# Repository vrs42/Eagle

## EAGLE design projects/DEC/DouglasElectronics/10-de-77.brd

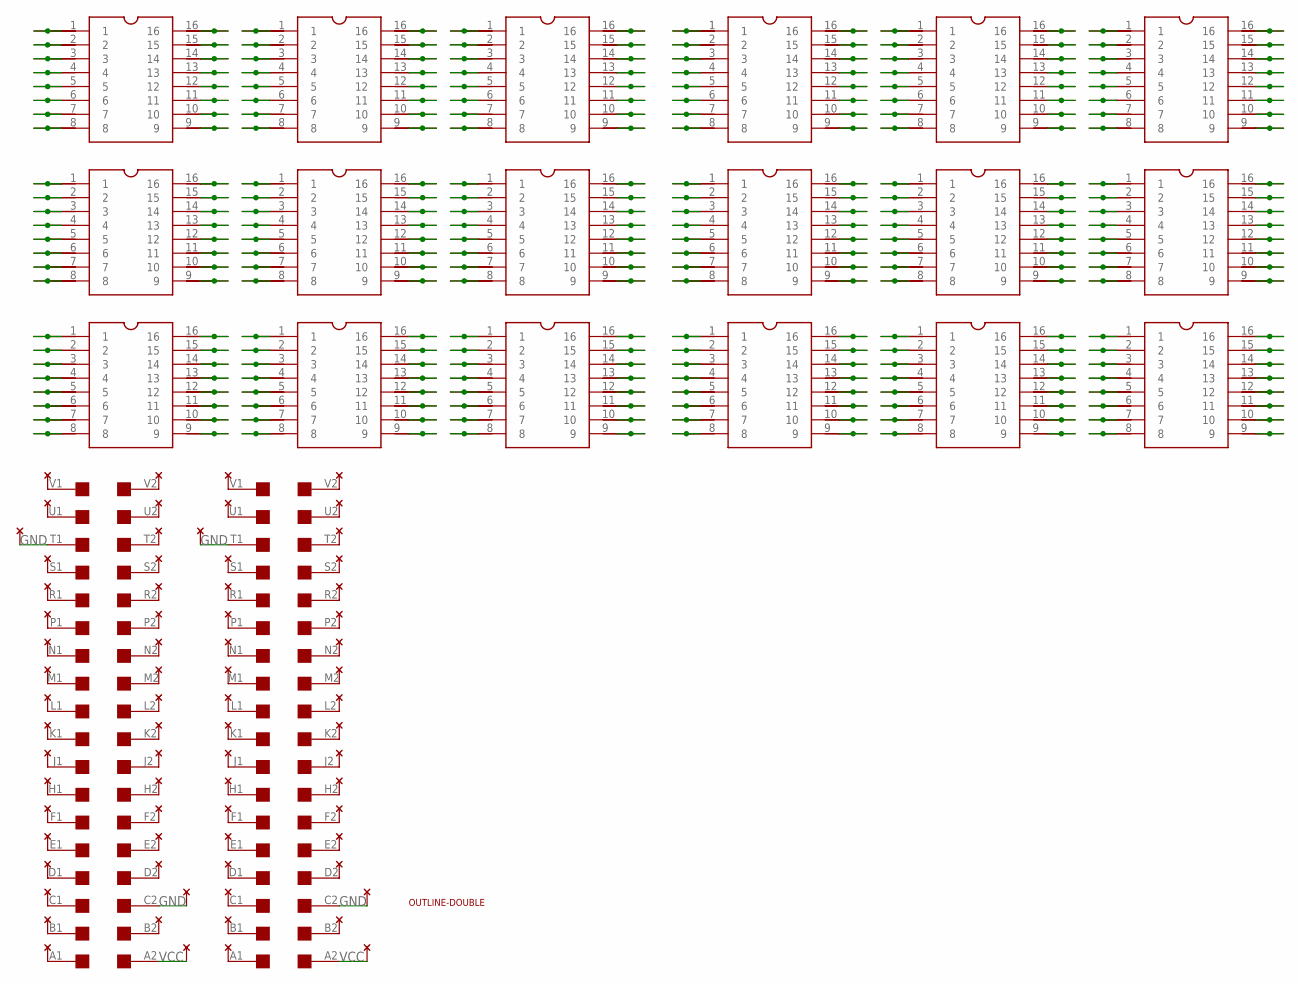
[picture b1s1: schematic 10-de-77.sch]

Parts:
U$1, U$6: SINGLE; EDGE-CON2
U$4: OUTLINE-DOUBLE; DOUBLE
U$5, U$7, U$8, U$9, U$10, U$11, U$12, U$13, U$14, U$15, U$16, U$17, U$18, U$19, U$20, U$21, U$22, U$23: DIL16PROTO
U$24, U$25, U$26, U$27: THRU-HOLE1A

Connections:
GND: U$1.C2, U$1.T1, U$6.C2, U$6.T1, U$24.T1, U$25.C1, U$26.T1, U$27.C1
unnamed: U$1.K2, U$25.K1
unnamed: U$1.J2, U$25.J1
unnamed: U$1.H2, U$25.H1
unnamed: U$1.L2, U$25.L1
unnamed: U$1.M2, U$25.M1
unnamed: U$1.N2, U$25.N1
unnamed: U$1.P2, U$25.P1
unnamed: U$1.F2, U$25.F1
unnamed: U$1.E2, U$25.E1
unnamed: U$1.D2, U$25.D1
unnamed: U$1.R2, U$25.R1
unnamed: U$1.S2, U$25.S1
unnamed: U$1.B2, U$25.B1
unnamed: U$1.T2, U$25.T1
unnamed: U$1.U2, U$25.U1
unnamed: U$1.V2, U$25.V1
unnamed: U$1.A1, U$24.A1
unnamed: U$1.V1, U$24.V1
unnamed: U$1.U1, U$24.U1
unnamed: U$1.S1, U$24.S1
unnamed: U$1.R1, U$24.R1
unnamed: U$1.P1, U$24.P1
unnamed: U$1.N1, U$24.N1
unnamed: U$1.M1, U$24.M1
unnamed: U$1.L1, U$24.L1
unnamed: U$1.K1, U$24.K1
unnamed: U$1.J1, U$24.J1
unnamed: U$1.H1, U$24.H1
unnamed: U$1.F1, U$24.F1
unnamed: U$1.E1, U$24.E1
unnamed: U$1.D1, U$24.D1
unnamed: U$1.C1, U$24.C1
unnamed: U$1.B1, U$24.B1
unnamed: U$6.K2, U$27.K1
unnamed: U$6.J2, U$27.J1
unnamed: U$6.H2, U$27.H1
unnamed: U$6.L2, U$27.L1
unnamed: U$6.M2, U$27.M1
unnamed: U$6.N2, U$27.N1
unnamed: U$6.P2, U$27.P1
unnamed: U$6.F2, U$27.F1
unnamed: U$6.E2, U$27.E1
unnamed: U$6.D2, U$27.D1
unnamed: U$6.R2, U$27.R1
unnamed: U$6.S2, U$27.S1
unnamed: U$6.B2, U$27.B1
unnamed: U$6.T2, U$27.T1
unnamed: U$6.U2, U$27.U1
unnamed: U$6.V2, U$27.V1
unnamed: U$6.A1, U$26.A1
unnamed: U$6.V1, U$26.V1
unnamed: U$6.U1, U$26.U1
unnamed: U$6.S1, U$26.S1
unnamed: U$6.R1, U$26.R1
unnamed: U$6.P1, U$26.P1
unnamed: U$6.N1, U$26.N1
unnamed: U$6.M1, U$26.M1
unnamed: U$6.L1, U$26.L1
unnamed: U$6.K1, U$26.K1
unnamed: U$6.J1, U$26.J1
unnamed: U$6.H1, U$26.H1
unnamed: U$6.F1, U$26.F1
unnamed: U$6.E1, U$26.E1
unnamed: U$6.D1, U$26.D1
unnamed: U$6.C1, U$26.C1
unnamed: U$6.B1, U$26.B1
unnamed: U$5.1, U$5.1@2 (1), U$5.1@3 (1)
unnamed: U$5.4, U$5.4@2 (4), U$5.4@3 (4)
unnamed: U$5.2, U$5.2@2 (2), U$5.2@3 (2)
unnamed: U$5.3, U$5.3@2 (3), U$5.3@3 (3)
unnamed: U$5.5, U$5.5@2 (5), U$5.5@3 (5)
unnamed: U$5.6, U$5.6@2 (6), U$5.6@3 (6)
unnamed: U$5.7, U$5.7@2 (7), U$5.7@3 (7)
unnamed: U$5.8, U$5.8@2 (8), U$5.8@3 (8)
unnamed: U$5.16, U$5.16@2 (16), U$5.16@3 (16)
unnamed: U$5.15, U$5.15@2 (15), U$5.15@3 (15)
unnamed: U$5.14, U$5.14@2 (14), U$5.14@3 (14)
unnamed: U$5.13, U$5.13@2 (13), U$5.13@3 (13)
unnamed: U$5.12, U$5.12@2 (12), U$5.12@3 (12)
unnamed: U$5.11, U$5.11@2 (11), U$5.11@3 (11)
unnamed: U$5.10, U$5.10@2 (10), U$5.10@3 (10)
unnamed: U$5.9, U$5.9@2 (9), U$5.9@3 (9)
unnamed: U$7.1, U$7.1@2 (1), U$7.1@3 (1)
unnamed: U$7.2, U$7.2@2 (2), U$7.2@3 (2)
unnamed: U$7.3, U$7.3@2 (3), U$7.3@3 (3)
unnamed: U$7.4, U$7.4@2 (4), U$7.4@3 (4)
unnamed: U$7.5, U$7.5@2 (5), U$7.5@3 (5)
unnamed: U$7.6, U$7.6@2 (6), U$7.6@3 (6)
unnamed: U$7.7, U$7.7@2 (7), U$7.7@3 (7)
unnamed: U$7.8, U$7.8@2 (8), U$7.8@3 (8)
unnamed: U$7.16, U$7.16@2 (16), U$7.16@3 (16)
unnamed: U$7.15, U$7.15@2 (15), U$7.15@3 (15)
unnamed: U$7.14, U$7.14@2 (14), U$7.14@3 (14)
unnamed: U$7.13, U$7.13@2 (13), U$7.13@3 (13)
unnamed: U$7.12, U$7.12@2 (12), U$7.12@3 (12)
unnamed: U$7.11, U$7.11@2 (11), U$7.11@3 (11)
unnamed: U$7.10, U$7.10@2 (10), U$7.10@3 (10)
unnamed: U$7.9, U$7.9@2 (9), U$7.9@3 (9)
unnamed: U$8.1, U$8.1@2 (1), U$8.1@3 (1)
unnamed: U$8.2, U$8.2@2 (2), U$8.2@3 (2)
unnamed: U$8.3, U$8.3@2 (3), U$8.3@3 (3)
unnamed: U$8.4, U$8.4@2 (4), U$8.4@3 (4)
unnamed: U$8.5, U$8.5@2 (5), U$8.5@3 (5)
unnamed: U$8.6, U$8.6@2 (6), U$8.6@3 (6)
unnamed: U$8.7, U$8.7@2 (7), U$8.7@3 (7)
unnamed: U$8.8, U$8.8@2 (8), U$8.8@3 (8)
unnamed: U$8.16, U$8.16@2 (16), U$8.16@3 (16)
unnamed: U$8.15, U$8.15@2 (15), U$8.15@3 (15)
unnamed: U$8.14, U$8.14@2 (14), U$8.14@3 (14)
unnamed: U$8.13, U$8.13@2 (13), U$8.13@3 (13)
unnamed: U$8.12, U$8.12@2 (12), U$8.12@3 (12)
unnamed: U$8.11, U$8.11@2 (11), U$8.11@3 (11)
unnamed: U$8.10, U$8.10@2 (10), U$8.10@3 (10)
unnamed: U$8.9, U$8.9@2 (9), U$8.9@3 (9)
unnamed: U$9.1, U$9.1@2 (1), U$9.1@3 (1)
unnamed: U$9.2, U$9.2@2 (2), U$9.2@3 (2)
unnamed: U$9.3, U$9.3@2 (3), U$9.3@3 (3)
unnamed: U$9.4, U$9.4@2 (4), U$9.4@3 (4)
unnamed: U$9.5, U$9.5@2 (5), U$9.5@3 (5)
unnamed: U$9.6, U$9.6@2 (6), U$9.6@3 (6)
unnamed: U$9.7, U$9.7@2 (7), U$9.7@3 (7)
unnamed: U$9.8, U$9.8@2 (8), U$9.8@3 (8)
unnamed: U$9.16, U$9.16@2 (16), U$9.16@3 (16)
unnamed: U$9.15, U$9.15@2 (15), U$9.15@3 (15)
unnamed: U$9.14, U$9.14@2 (14), U$9.14@3 (14)
unnamed: U$9.13, U$9.13@2 (13), U$9.13@3 (13)
unnamed: U$9.12, U$9.12@2 (12), U$9.12@3 (12)
unnamed: U$9.11, U$9.11@2 (11), U$9.11@3 (11)
unnamed: U$9.10, U$9.10@2 (10), U$9.10@3 (10)
unnamed: U$9.9, U$9.9@2 (9), U$9.9@3 (9)
unnamed: U$10.1, U$10.1@2 (1), U$10.1@3 (1)
unnamed: U$10.2, U$10.2@2 (2), U$10.2@3 (2)
unnamed: U$10.3, U$10.3@2 (3), U$10.3@3 (3)
unnamed: U$10.4, U$10.4@2 (4), U$10.4@3 (4)
unnamed: U$10.5, U$10.5@2 (5), U$10.5@3 (5)
unnamed: U$10.6, U$10.6@2 (6), U$10.6@3 (6)
unnamed: U$10.7, U$10.7@2 (7), U$10.7@3 (7)
unnamed: U$10.8, U$10.8@2 (8), U$10.8@3 (8)
unnamed: U$10.16, U$10.16@2 (16), U$10.16@3 (16)
unnamed: U$10.15, U$10.15@2 (15), U$10.15@3 (15)
unnamed: U$10.14, U$10.14@2 (14), U$10.14@3 (14)
unnamed: U$10.13, U$10.13@2 (13), U$10.13@3 (13)
unnamed: U$10.12, U$10.12@2 (12), U$10.12@3 (12)
unnamed: U$10.11, U$10.11@2 (11), U$10.11@3 (11)
unnamed: U$10.10, U$10.10@2 (10), U$10.10@3 (10)
unnamed: U$10.9, U$10.9@2 (9), U$10.9@3 (9)
unnamed: U$11.1, U$11.1@2 (1), U$11.1@3 (1)
unnamed: U$11.2, U$11.2@2 (2), U$11.2@3 (2)
unnamed: U$11.3, U$11.3@2 (3), U$11.3@3 (3)
unnamed: U$11.4, U$11.4@2 (4), U$11.4@3 (4)
unnamed: U$11.5, U$11.5@2 (5), U$11.5@3 (5)
unnamed: U$11.6, U$11.6@2 (6), U$11.6@3 (6)
unnamed: U$11.7, U$11.7@2 (7), U$11.7@3 (7)
unnamed: U$11.8, U$11.8@2 (8), U$11.8@3 (8)
unnamed: U$11.16, U$11.16@2 (16), U$11.16@3 (16)
unnamed: U$11.15, U$11.15@2 (15), U$11.15@3 (15)
unnamed: U$11.14, U$11.14@2 (14), U$11.14@3 (14)
unnamed: U$11.13, U$11.13@2 (13), U$11.13@3 (13)
unnamed: U$11.12, U$11.12@2 (12), U$11.12@3 (12)
unnamed: U$11.11, U$11.11@2 (11), U$11.11@3 (11)
unnamed: U$11.10, U$11.10@2 (10), U$11.10@3 (10)
unnamed: U$11.9, U$11.9@2 (9), U$11.9@3 (9)
unnamed: U$12.1, U$12.1@2 (1), U$12.1@3 (1)
unnamed: U$12.2, U$12.2@2 (2), U$12.2@3 (2)
unnamed: U$12.3, U$12.3@2 (3), U$12.3@3 (3)
unnamed: U$12.4, U$12.4@2 (4), U$12.4@3 (4)
unnamed: U$12.5, U$12.5@2 (5), U$12.5@3 (5)
unnamed: U$12.6, U$12.6@2 (6), U$12.6@3 (6)
unnamed: U$12.7, U$12.7@2 (7), U$12.7@3 (7)
unnamed: U$12.8, U$12.8@2 (8), U$12.8@3 (8)
unnamed: U$12.16, U$12.16@2 (16), U$12.16@3 (16)
unnamed: U$12.15, U$12.15@2 (15), U$12.15@3 (15)
unnamed: U$12.14, U$12.14@2 (14), U$12.14@3 (14)
unnamed: U$12.13, U$12.13@2 (13), U$12.13@3 (13)
unnamed: U$12.12, U$12.12@2 (12), U$12.12@3 (12)
unnamed: U$12.11, U$12.11@2 (11), U$12.11@3 (11)
unnamed: U$12.10, U$12.10@2 (10), U$12.10@3 (10)
unnamed: U$12.9, U$12.9@2 (9), U$12.9@3 (9)
unnamed: U$13.1, U$13.1@2 (1), U$13.1@3 (1)
unnamed: U$13.2, U$13.2@2 (2), U$13.2@3 (2)
unnamed: U$13.3, U$13.3@2 (3), U$13.3@3 (3)
unnamed: U$13.4, U$13.4@2 (4), U$13.4@3 (4)
unnamed: U$13.5, U$13.5@2 (5), U$13.5@3 (5)
unnamed: U$13.6, U$13.6@2 (6), U$13.6@3 (6)
unnamed: U$13.7, U$13.7@2 (7), U$13.7@3 (7)
unnamed: U$13.8, U$13.8@2 (8), U$13.8@3 (8)
unnamed: U$13.16, U$13.16@2 (16), U$13.16@3 (16)
unnamed: U$13.15, U$13.15@2 (15), U$13.15@3 (15)
unnamed: U$13.14, U$13.14@2 (14), U$13.14@3 (14)
unnamed: U$13.13, U$13.13@2 (13), U$13.13@3 (13)
unnamed: U$13.12, U$13.12@2 (12), U$13.12@3 (12)
unnamed: U$13.11, U$13.11@2 (11), U$13.11@3 (11)
unnamed: U$13.10, U$13.10@2 (10), U$13.10@3 (10)
unnamed: U$13.9, U$13.9@2 (9), U$13.9@3 (9)
unnamed: U$14.1, U$14.1@2 (1), U$14.1@3 (1)
unnamed: U$14.2, U$14.2@2 (2), U$14.2@3 (2)
unnamed: U$14.3, U$14.3@2 (3), U$14.3@3 (3)
unnamed: U$14.4, U$14.4@2 (4), U$14.4@3 (4)
unnamed: U$14.5, U$14.5@2 (5), U$14.5@3 (5)
unnamed: U$14.6, U$14.6@2 (6), U$14.6@3 (6)
unnamed: U$14.7, U$14.7@2 (7), U$14.7@3 (7)
unnamed: U$14.8, U$14.8@2 (8), U$14.8@3 (8)
unnamed: U$14.16, U$14.16@2 (16), U$14.16@3 (16)
unnamed: U$14.15, U$14.15@2 (15), U$14.15@3 (15)
unnamed: U$14.14, U$14.14@2 (14), U$14.14@3 (14)
unnamed: U$14.13, U$14.13@2 (13), U$14.13@3 (13)
unnamed: U$14.12, U$14.12@2 (12), U$14.12@3 (12)
unnamed: U$14.11, U$14.11@2 (11), U$14.11@3 (11)
unnamed: U$14.10, U$14.10@2 (10), U$14.10@3 (10)
unnamed: U$14.9, U$14.9@2 (9), U$14.9@3 (9)
unnamed: U$15.1, U$15.1@2 (1), U$15.1@3 (1)
unnamed: U$15.2, U$15.2@2 (2), U$15.2@3 (2)
unnamed: U$15.3, U$15.3@2 (3), U$15.3@3 (3)
unnamed: U$15.4, U$15.4@2 (4), U$15.4@3 (4)
unnamed: U$15.5, U$15.5@2 (5), U$15.5@3 (5)
unnamed: U$15.6, U$15.6@2 (6), U$15.6@3 (6)
unnamed: U$15.7, U$15.7@2 (7), U$15.7@3 (7)
unnamed: U$15.8, U$15.8@2 (8), U$15.8@3 (8)
unnamed: U$15.16, U$15.16@2 (16), U$15.16@3 (16)
unnamed: U$15.15, U$15.15@2 (15), U$15.15@3 (15)
unnamed: U$15.14, U$15.14@2 (14), U$15.14@3 (14)
unnamed: U$15.13, U$15.13@2 (13), U$15.13@3 (13)
unnamed: U$15.12, U$15.12@2 (12), U$15.12@3 (12)
unnamed: U$15.11, U$15.11@2 (11), U$15.11@3 (11)
unnamed: U$15.10, U$15.10@2 (10), U$15.10@3 (10)
unnamed: U$15.9, U$15.9@2 (9), U$15.9@3 (9)
unnamed: U$16.1, U$16.1@2 (1), U$16.1@3 (1)
unnamed: U$16.2, U$16.2@2 (2), U$16.2@3 (2)
unnamed: U$16.3, U$16.3@2 (3), U$16.3@3 (3)
unnamed: U$16.4, U$16.4@2 (4), U$16.4@3 (4)
unnamed: U$16.5, U$16.5@2 (5), U$16.5@3 (5)
unnamed: U$16.6, U$16.6@2 (6), U$16.6@3 (6)
unnamed: U$16.7, U$16.7@2 (7), U$16.7@3 (7)
unnamed: U$16.8, U$16.8@2 (8), U$16.8@3 (8)
unnamed: U$16.16, U$16.16@2 (16), U$16.16@3 (16)
unnamed: U$16.15, U$16.15@2 (15), U$16.15@3 (15)
unnamed: U$16.14, U$16.14@2 (14), U$16.14@3 (14)
unnamed: U$16.13, U$16.13@2 (13), U$16.13@3 (13)
unnamed: U$16.12, U$16.12@2 (12), U$16.12@3 (12)
unnamed: U$16.11, U$16.11@2 (11), U$16.11@3 (11)
unnamed: U$16.10, U$16.10@2 (10), U$16.10@3 (10)
unnamed: U$16.9, U$16.9@2 (9), U$16.9@3 (9)
unnamed: U$17.1, U$17.1@2 (1), U$17.1@3 (1)
unnamed: U$17.2, U$17.2@2 (2), U$17.2@3 (2)
unnamed: U$17.3, U$17.3@2 (3), U$17.3@3 (3)
unnamed: U$17.4, U$17.4@2 (4), U$17.4@3 (4)
unnamed: U$17.5, U$17.5@2 (5), U$17.5@3 (5)
unnamed: U$17.6, U$17.6@2 (6), U$17.6@3 (6)
unnamed: U$17.7, U$17.7@2 (7), U$17.7@3 (7)
unnamed: U$17.8, U$17.8@2 (8), U$17.8@3 (8)
unnamed: U$17.16, U$17.16@2 (16), U$17.16@3 (16)
unnamed: U$17.15, U$17.15@2 (15), U$17.15@3 (15)
unnamed: U$17.14, U$17.14@2 (14), U$17.14@3 (14)
unnamed: U$17.13, U$17.13@2 (13), U$17.13@3 (13)
unnamed: U$17.12, U$17.12@2 (12), U$17.12@3 (12)
unnamed: U$17.11, U$17.11@2 (11), U$17.11@3 (11)
unnamed: U$17.10, U$17.10@2 (10), U$17.10@3 (10)
unnamed: U$17.9, U$17.9@2 (9), U$17.9@3 (9)
unnamed: U$18.1, U$18.1@2 (1), U$18.1@3 (1)
unnamed: U$18.2, U$18.2@2 (2), U$18.2@3 (2)
unnamed: U$18.3, U$18.3@2 (3), U$18.3@3 (3)
unnamed: U$18.4, U$18.4@2 (4), U$18.4@3 (4)
unnamed: U$18.5, U$18.5@2 (5), U$18.5@3 (5)
unnamed: U$18.6, U$18.6@2 (6), U$18.6@3 (6)
unnamed: U$18.7, U$18.7@2 (7), U$18.7@3 (7)
unnamed: U$18.8, U$18.8@2 (8), U$18.8@3 (8)
unnamed: U$18.16, U$18.16@2 (16), U$18.16@3 (16)
unnamed: U$18.15, U$18.15@2 (15), U$18.15@3 (15)
unnamed: U$18.14, U$18.14@2 (14), U$18.14@3 (14)
unnamed: U$18.13, U$18.13@2 (13), U$18.13@3 (13)
unnamed: U$18.12, U$18.12@2 (12), U$18.12@3 (12)
unnamed: U$18.11, U$18.11@2 (11), U$18.11@3 (11)
unnamed: U$18.10, U$18.10@2 (10), U$18.10@3 (10)
unnamed: U$18.9, U$18.9@2 (9), U$18.9@3 (9)
unnamed: U$19.1, U$19.1@2 (1), U$19.1@3 (1)
unnamed: U$19.2, U$19.2@2 (2), U$19.2@3 (2)
unnamed: U$19.3, U$19.3@2 (3), U$19.3@3 (3)
unnamed: U$19.4, U$19.4@2 (4), U$19.4@3 (4)
unnamed: U$19.5, U$19.5@2 (5), U$19.5@3 (5)
unnamed: U$19.6, U$19.6@2 (6), U$19.6@3 (6)
unnamed: U$19.7, U$19.7@2 (7), U$19.7@3 (7)
unnamed: U$19.8, U$19.8@2 (8), U$19.8@3 (8)
unnamed: U$19.16, U$19.16@2 (16), U$19.16@3 (16)
unnamed: U$19.15, U$19.15@2 (15), U$19.15@3 (15)
unnamed: U$19.14, U$19.14@2 (14), U$19.14@3 (14)
unnamed: U$19.13, U$19.13@2 (13), U$19.13@3 (13)
unnamed: U$19.12, U$19.12@2 (12), U$19.12@3 (12)
unnamed: U$19.11, U$19.11@2 (11), U$19.11@3 (11)
unnamed: U$19.10, U$19.10@2 (10), U$19.10@3 (10)
unnamed: U$19.9, U$19.9@2 (9), U$19.9@3 (9)
unnamed: U$20.1, U$20.1@2 (1), U$20.1@3 (1)
unnamed: U$20.2, U$20.2@2 (2), U$20.2@3 (2)
unnamed: U$20.3, U$20.3@2 (3), U$20.3@3 (3)
unnamed: U$20.4, U$20.4@2 (4), U$20.4@3 (4)
unnamed: U$20.5, U$20.5@2 (5), U$20.5@3 (5)
unnamed: U$20.6, U$20.6@2 (6), U$20.6@3 (6)
unnamed: U$20.7, U$20.7@2 (7), U$20.7@3 (7)
unnamed: U$20.8, U$20.8@2 (8), U$20.8@3 (8)
unnamed: U$20.16, U$20.16@2 (16), U$20.16@3 (16)
unnamed: U$20.15, U$20.15@2 (15), U$20.15@3 (15)
unnamed: U$20.14, U$20.14@2 (14), U$20.14@3 (14)
unnamed: U$20.13, U$20.13@2 (13), U$20.13@3 (13)
unnamed: U$20.12, U$20.12@2 (12), U$20.12@3 (12)
unnamed: U$20.11, U$20.11@2 (11), U$20.11@3 (11)
unnamed: U$20.10, U$20.10@2 (10), U$20.10@3 (10)
unnamed: U$20.9, U$20.9@2 (9), U$20.9@3 (9)
unnamed: U$21.1, U$21.1@2 (1), U$21.1@3 (1)
unnamed: U$21.2, U$21.2@2 (2), U$21.2@3 (2)
unnamed: U$21.3, U$21.3@2 (3), U$21.3@3 (3)
unnamed: U$21.4, U$21.4@2 (4), U$21.4@3 (4)
unnamed: U$21.5, U$21.5@2 (5), U$21.5@3 (5)
unnamed: U$21.6, U$21.6@2 (6), U$21.6@3 (6)
unnamed: U$21.7, U$21.7@2 (7), U$21.7@3 (7)
unnamed: U$21.8, U$21.8@2 (8), U$21.8@3 (8)
unnamed: U$21.16, U$21.16@2 (16), U$21.16@3 (16)
unnamed: U$21.15, U$21.15@2 (15), U$21.15@3 (15)
unnamed: U$21.14, U$21.14@2 (14), U$21.14@3 (14)
unnamed: U$21.13, U$21.13@2 (13), U$21.13@3 (13)
unnamed: U$21.12, U$21.12@2 (12), U$21.12@3 (12)
unnamed: U$21.11, U$21.11@2 (11), U$21.11@3 (11)
unnamed: U$21.10, U$21.10@2 (10), U$21.10@3 (10)
unnamed: U$21.9, U$21.9@2 (9), U$21.9@3 (9)
unnamed: U$22.1, U$22.1@2 (1), U$22.1@3 (1)
unnamed: U$22.2, U$22.2@2 (2), U$22.2@3 (2)
unnamed: U$22.3, U$22.3@2 (3), U$22.3@3 (3)
unnamed: U$22.4, U$22.4@2 (4), U$22.4@3 (4)
unnamed: U$22.5, U$22.5@2 (5), U$22.5@3 (5)
unnamed: U$22.6, U$22.6@2 (6), U$22.6@3 (6)
unnamed: U$22.7, U$22.7@2 (7), U$22.7@3 (7)
unnamed: U$22.8, U$22.8@2 (8), U$22.8@3 (8)
unnamed: U$22.16, U$22.16@2 (16), U$22.16@3 (16)
unnamed: U$22.15, U$22.15@2 (15), U$22.15@3 (15)
unnamed: U$22.14, U$22.14@2 (14), U$22.14@3 (14)
unnamed: U$22.13, U$22.13@2 (13), U$22.13@3 (13)
unnamed: U$22.12, U$22.12@2 (12), U$22.12@3 (12)
unnamed: U$22.11, U$22.11@2 (11), U$22.11@3 (11)
unnamed: U$22.10, U$22.10@2 (10), U$22.10@3 (10)
unnamed: U$22.9, U$22.9@2 (9), U$22.9@3 (9)
unnamed: U$23.1, U$23.1@2 (1), U$23.1@3 (1)
unnamed: U$23.2, U$23.2@2 (2), U$23.2@3 (2)
unnamed: U$23.3, U$23.3@2 (3), U$23.3@3 (3)
unnamed: U$23.4, U$23.4@2 (4), U$23.4@3 (4)
unnamed: U$23.5, U$23.5@2 (5), U$23.5@3 (5)
unnamed: U$23.6, U$23.6@2 (6), U$23.6@3 (6)
unnamed: U$23.7, U$23.7@2 (7), U$23.7@3 (7)
unnamed: U$23.8, U$23.8@2 (8), U$23.8@3 (8)
unnamed: U$23.16, U$23.16@2 (16), U$23.16@3 (16)
unnamed: U$23.15, U$23.15@2 (15), U$23.15@3 (15)
unnamed: U$23.14, U$23.14@2 (14), U$23.14@3 (14)
unnamed: U$23.13, U$23.13@2 (13), U$23.13@3 (13)
unnamed: U$23.12, U$23.12@2 (12), U$23.12@3 (12)
unnamed: U$23.11, U$23.11@2 (11), U$23.11@3 (11)
unnamed: U$23.10, U$23.10@2 (10), U$23.10@3 (10)
unnamed: U$23.9, U$23.9@2 (9), U$23.9@3 (9)
VCC: U$1.A2, U$6.A2, U$25.A1, U$27.A1

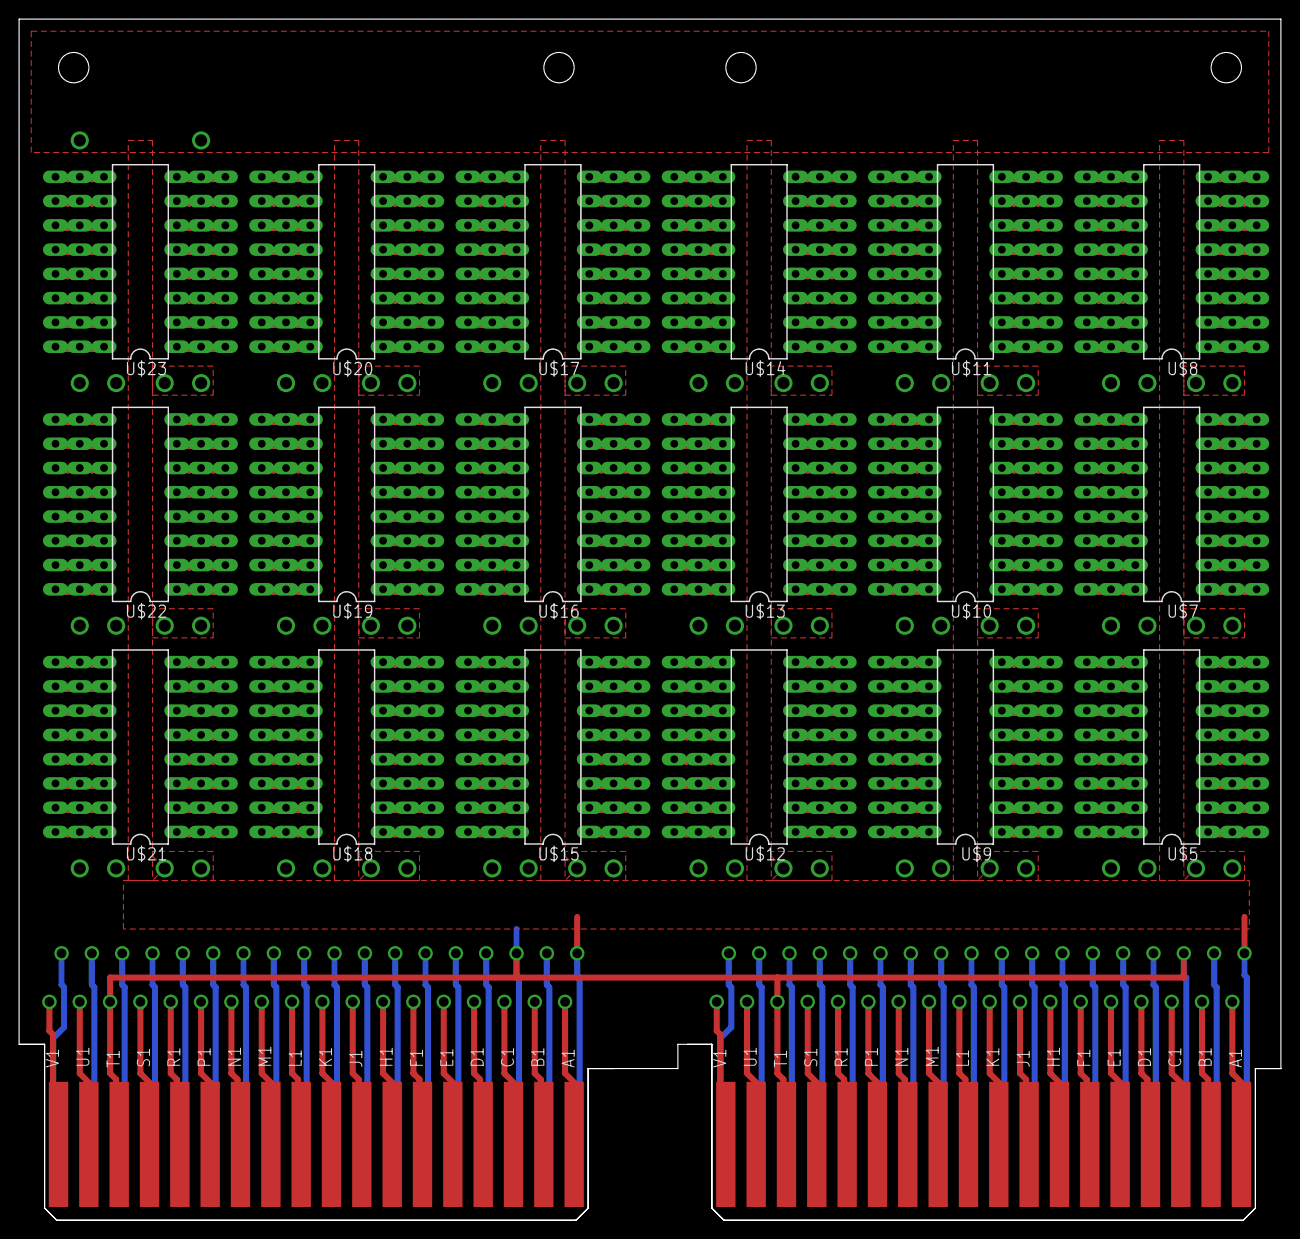
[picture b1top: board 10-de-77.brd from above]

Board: 2 copper layers, 132.1 x 125.7 mm, 25 parts (0 on the bottom side), 356 nets.

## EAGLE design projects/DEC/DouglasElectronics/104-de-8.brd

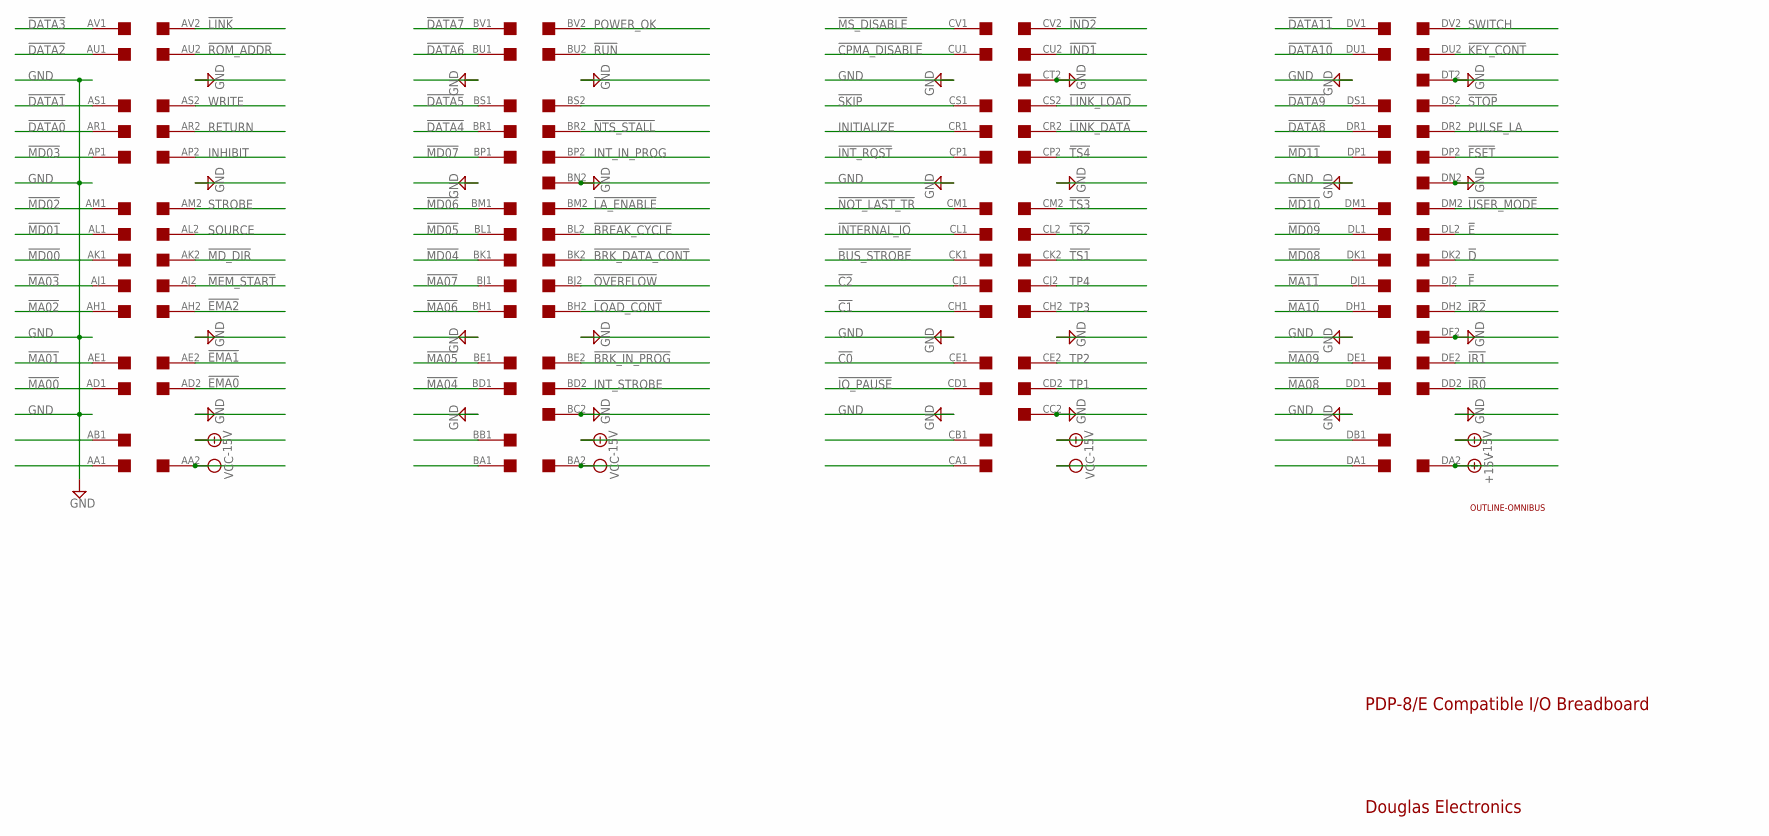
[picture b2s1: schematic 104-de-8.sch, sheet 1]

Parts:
U$1: OUTLINE-OMNIBUS; OMNIBUS
U$2: QUAD; EDGE-CON8

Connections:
!BREAK_CYCLE: U$2.BL2
!BRK_DATA_CONT: U$2.BK2
!BRK_IN_PROG: U$2.BE2
!BUS_STROBE: U$2.CK1
!C0: U$2.CE1
!C1: U$2.CH1
!C2: U$2.CJ1
!CPMA_DISABLE: U$2.CU1
!D: U$2.DK2
!DATA0: U$2.AR1
!DATA1: U$2.AS1
!DATA2: U$2.AU1
!DATA3: U$2.AV1
!DATA4: U$2.BR1
!DATA5: U$2.BS1
!DATA6: U$2.BU1
!DATA7: U$2.BV1
!DATA8: U$2.DR1
!DATA9: U$2.DS1
!DATA10: U$2.DU1
!DATA11: U$2.DV1
!E: U$2.DL2
!EMA0: U$2.AD2; also elsewhere on the board
!EMA1: U$2.AE2; also elsewhere on the board
!EMA2: U$2.AH2; also elsewhere on the board
!F: U$2.DJ2
!FSET: U$2.DP2
!IND1: U$2.CU2
!IND2: U$2.CV2
!INTERNAL_IO: U$2.CL1
!INT_RQST: U$2.CP1
!IO_PAUSE: U$2.CD1
!IR0: U$2.DD2
!IR1: U$2.DE2
!IR2: U$2.DH2
!KEY_CONT: U$2.DU2
!LA_ENABLE: U$2.BM2
!LINK: U$2.AV2
!LINK_DATA: U$2.CR2
!LINK_LOAD: U$2.CS2
!LOAD_CONT: U$2.BH2
!MA00: U$2.AD1; also elsewhere on the board
!MA01: U$2.AE1; also elsewhere on the board
!MA02: U$2.AH1; also elsewhere on the board
!MA03: U$2.AJ1; also elsewhere on the board
!MA04: U$2.BD1; also elsewhere on the board
!MA05: U$2.BE1; also elsewhere on the board
!MA06: U$2.BH1; also elsewhere on the board
!MA07: U$2.BJ1; also elsewhere on the board
!MA08: U$2.DD1; also elsewhere on the board
!MA09: U$2.DE1; also elsewhere on the board
!MA10: U$2.DH1; also elsewhere on the board
!MA11: U$2.DJ1; also elsewhere on the board
!MD00: U$2.AK1
!MD01: U$2.AL1
!MD02: U$2.AM1
!MD03: U$2.AP1
!MD04: U$2.BK1
!MD05: U$2.BL1
!MD06: U$2.BM1
!MD07: U$2.BP1
!MD08: U$2.DK1
!MD09: U$2.DL1
!MD10: U$2.DM1
!MD11: U$2.DP1
!MD_DIR: U$2.AK2; also elsewhere on the board
!MEM_START: U$2.AJ2
!MS_DISABLE: U$2.CV1
!NOT_LAST_TR: U$2.CM1
!NTS_STALL: U$2.BR2
!OVERFLOW: U$2.BJ2
!ROM_ADDR: U$2.AU2
!RUN: U$2.BU2
!SKIP: U$2.CS1
!STOP: U$2.DS2
!TS1: U$2.CK2
!TS2: U$2.CL2
!TS3: U$2.CM2
!TS4: U$2.CP2
!USER_MODE: U$2.DM2
+15V: U$2.DA2
GND: U$2.BC2, U$2.BN2, U$2.CC2, U$2.CT2, U$2.DF2, U$2.DN2, U$2.DT2; also elsewhere on the board
INHIBIT: U$2.AP2
INITIALIZE: U$2.CR1
INT_IN_PROG: U$2.BP2
INT_STROBE: U$2.BD2
POWER_OK: U$2.BV2
PULSE_LA: U$2.DR2
RETURN: U$2.AR2
SOURCE: U$2.AL2
STROBE: U$2.AM2
SWITCH: U$2.DV2
TP1: U$2.CD2
TP2: U$2.CE2
TP3: U$2.CH2
TP4: U$2.CJ2
VCC: U$2.AA2, U$2.BA2; also elsewhere on the board
WRITE: U$2.AS2

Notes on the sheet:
PDP-8/E Compatible I/O Breadboard
Douglas Electronics

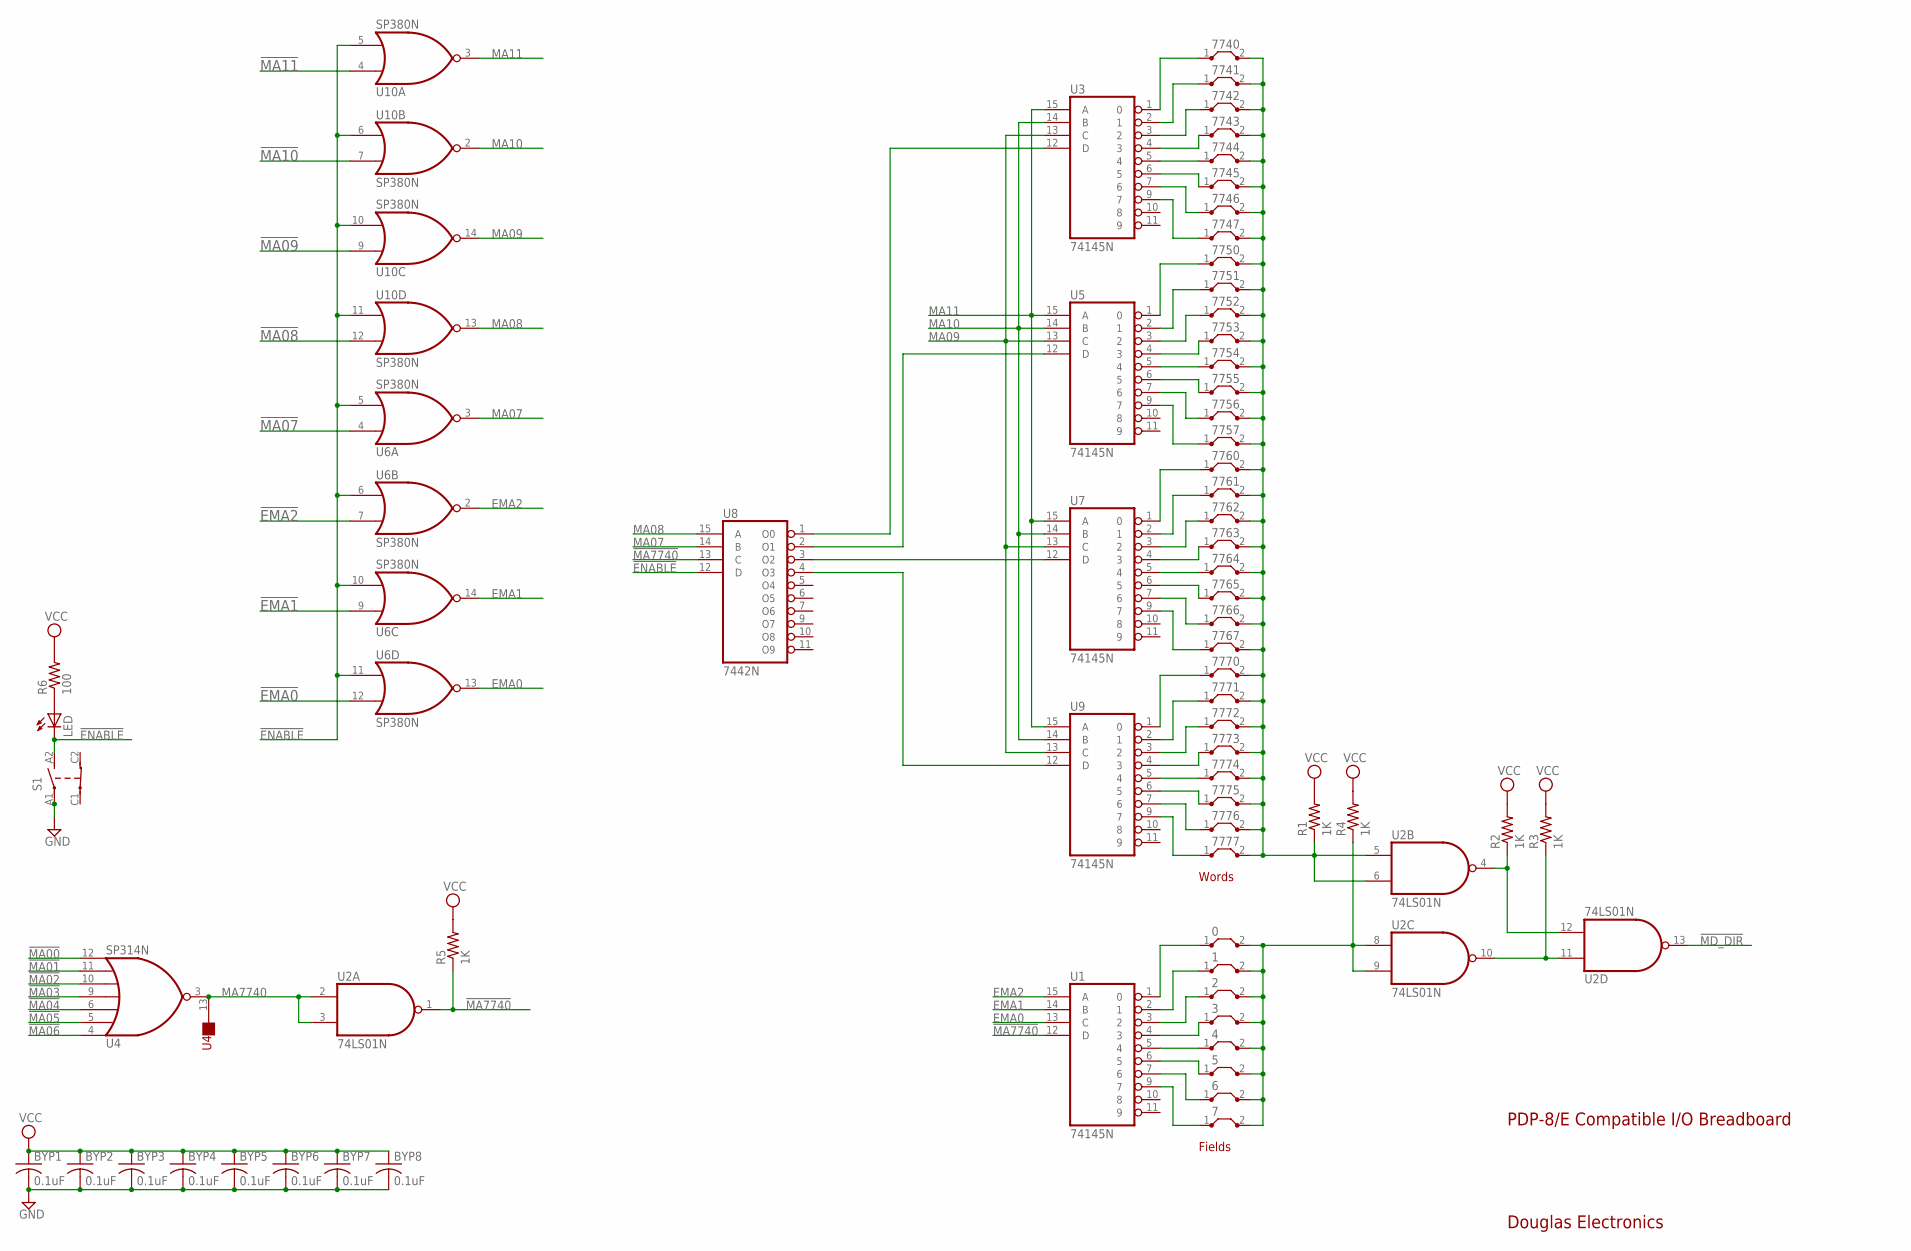
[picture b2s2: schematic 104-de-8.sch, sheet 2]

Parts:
0, 1, 2, 3, 4, 5, 6, 7, 7740, 7741, 7742, 7743, 7744, 7745, 7746, 7747, 7750, 7751, 7752, 7753, 7754, 7755, 7756, 7757, 7760, 7761, 7762, 7763, 7764, 7765, 7766, 7767, 7770, 7771, 7772, 7773, 7774, 7775, 7776, 7777: J5MM; 05
BYP1, BYP2, BYP3, BYP4, BYP5, BYP6, BYP7, BYP8: 0.1uF; C063-025X075
LED: LED5MM
R1, R2, R3, R4, R5: 1K; 0207/10
R6: 100; 0207/10
S1: T8201; T8000
U1, U3, U5, U7, U9: 74145N; DIL16
U2: 74LS01N; DIL14
U4: SP314N; DIL14
U6, U10: SP380N; DIL14
U8: 7442N; DIL16

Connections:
!EMA0: U6.12 (I1); also elsewhere on the board
!EMA1: U6.9 (I0); also elsewhere on the board
!EMA2: U6.7 (I1); also elsewhere on the board
!ENABLE: LED.K (C), S1.A2, U6.5 (I1), U6.6 (I0), U6.10 (I1), U6.11 (I0), U8.12 (D), U10.5 (I1), U10.6 (I0), U10.10 (I1), U10.11 (I0)
!MA00: U4.12 (I6); also elsewhere on the board
!MA01: U4.11 (I5); also elsewhere on the board
!MA02: U4.10 (I4); also elsewhere on the board
!MA03: U4.9 (I3); also elsewhere on the board
!MA04: U4.6 (I2); also elsewhere on the board
!MA05: U4.5 (I1); also elsewhere on the board
!MA06: U4.4 (I0); also elsewhere on the board
!MA07: U6.4 (I0); also elsewhere on the board
!MA08: U10.12 (I1); also elsewhere on the board
!MA09: U10.9 (I0); also elsewhere on the board
!MA10: U10.7 (I1); also elsewhere on the board
!MA11: U10.4 (I0); also elsewhere on the board
!MA7740: R5.1, U1.12 (D), U2.1 (O), U8.13 (C)
!MD_DIR: U2.13 (O); also elsewhere on the board
EMA0: U1.13 (C), U6.13 (O)
EMA1: U1.14 (B), U6.14 (O)
EMA2: U1.15 (A), U6.2 (O)
GND: BYP1.2, BYP2.2, BYP3.2, BYP4.2, BYP5.2, BYP6.2, BYP7.2, BYP8.2, S1.A1, U1.8 (GND), U2.7 (GND), U3.8 (GND), U4.1 (GND), U5.8 (GND), U6.1 (GND), U7.8 (GND), U8.8 (GND), U9.8 (GND), U10.1 (GND); also elsewhere on the board
MA07: U6.3 (O), U8.14 (B)
MA08: U8.15 (A), U10.13 (O)
MA09: U3.13 (C), U5.13 (C), U7.13 (C), U9.13 (C), U10.14 (O)
MA10: U3.14 (B), U5.14 (B), U7.14 (B), U9.14 (B), U10.2 (O)
MA11: U3.15 (A), U5.15 (A), U7.15 (A), U9.15 (A), U10.3 (O)
MA7740: U2.2 (I0), U2.3 (I1), U4.3 (O), U4.13 (NC)
unnamed: LED.A, R6.1
unnamed: U8.4 (O3), U9.12 (D)
unnamed: U5.12 (D), U8.2 (O1)
unnamed: U7.12 (D), U8.3 (O2)
unnamed: U3.12 (D), U8.1 (O0)
unnamed: 7740.2, 7741.2, 7742.2, 7743.2, 7744.2, 7745.2, 7746.2, 7747.2, 7750.2, 7751.2, 7752.2, 7753.2, 7754.2, 7755.2, 7756.2, 7757.2, 7760.2, 7761.2, 7762.2, 7763.2, 7764.2, 7765.2, 7766.2, 7767.2, 7770.2, 7771.2, 7772.2, 7773.2, 7774.2, 7775.2, 7776.2, 7777.2, R1.1, U2.5 (I0), U2.6 (I1)
unnamed: R2.1, U2.4 (O), U2.12 (I1)
unnamed: R3.1, U2.10 (O), U2.11 (I0)
unnamed: 0.1, U1.1 (0)
unnamed: 0.2, 1.2, 2.2, 3.2, 4.2, 5.2, 6.2, 7.2, R4.1, U2.8 (I0), U2.9 (I1)
unnamed: 1.1, U1.2 (1)
unnamed: 2.1, U1.3 (2)
unnamed: 3.1, U1.4 (3)
unnamed: 4.1, U1.5 (4)
unnamed: 6.1, U1.7 (6)
unnamed: 7.1, U1.9 (7)
unnamed: 5.1, U1.6 (5)
unnamed: 7740.1, U3.1 (0)
unnamed: 7741.1, U3.2 (1)
unnamed: 7742.1, U3.3 (2)
unnamed: 7743.1, U3.4 (3)
unnamed: 7744.1, U3.5 (4)
unnamed: 7745.1, U3.6 (5)
unnamed: 7746.1, U3.7 (6)
unnamed: 7747.1, U3.9 (7)
unnamed: 7750.1, U5.1 (0)
unnamed: 7751.1, U5.2 (1)
unnamed: 7752.1, U5.3 (2)
unnamed: 7753.1, U5.4 (3)
unnamed: 7754.1, U5.5 (4)
unnamed: 7755.1, U5.6 (5)
unnamed: 7756.1, U5.7 (6)
unnamed: 7757.1, U5.9 (7)
unnamed: 7760.1, U7.1 (0)
unnamed: 7761.1, U7.2 (1)
unnamed: 7762.1, U7.3 (2)
unnamed: 7763.1, U7.4 (3)
unnamed: 7764.1, U7.5 (4)
unnamed: 7765.1, U7.6 (5)
unnamed: 7766.1, U7.7 (6)
unnamed: 7767.1, U7.9 (7)
unnamed: 7770.1, U9.1 (0)
unnamed: 7771.1, U9.2 (1)
unnamed: 7772.1, U9.3 (2)
unnamed: 7773.1, U9.4 (3)
unnamed: 7774.1, U9.5 (4)
unnamed: 7775.1, U9.6 (5)
unnamed: 7776.1, U9.7 (6)
unnamed: 7777.1, U9.9 (7)
VCC: BYP1.1, BYP2.1, BYP3.1, BYP4.1, BYP5.1, BYP6.1, BYP7.1, BYP8.1, R1.2, R2.2, R3.2, R4.2, R5.2, R6.2, U1.16 (VCC), U2.14 (VCC), U3.16 (VCC), U4.8 (VCC), U5.16 (VCC), U6.8 (VCC), U7.16 (VCC), U8.16 (VCC), U9.16 (VCC), U10.8 (VCC); also elsewhere on the board

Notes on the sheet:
PDP-8/E Compatible I/O Breadboard
Douglas Electronics
Fields
Words

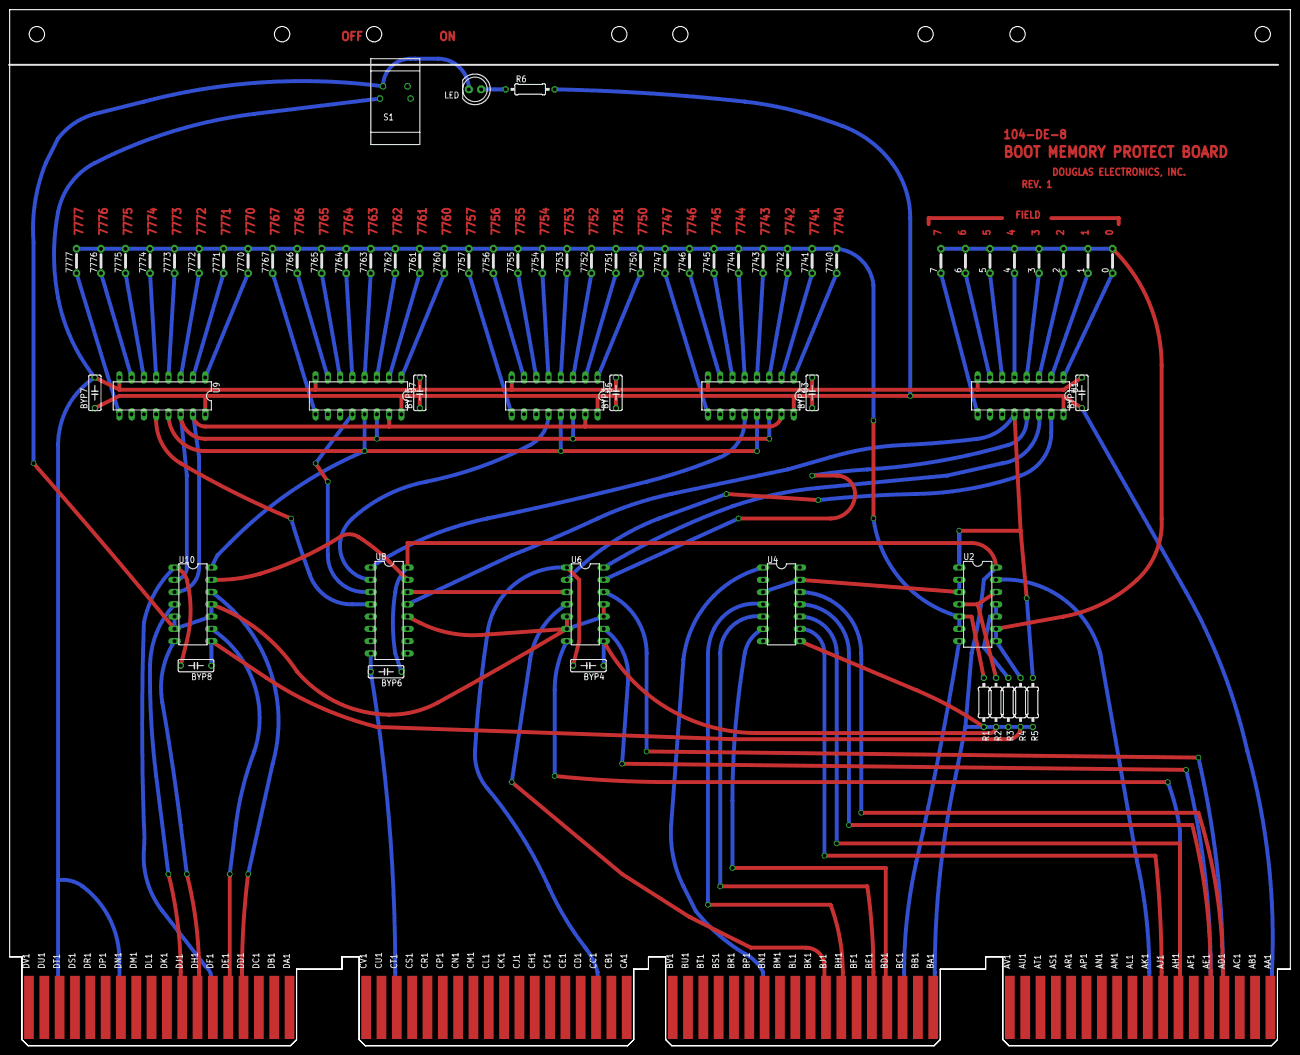
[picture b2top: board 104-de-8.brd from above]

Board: 3 copper layers, 265.3 x 214.6 mm, 68 parts (0 on the bottom side), 78 nets.
